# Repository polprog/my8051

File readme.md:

my8051
======

This project contains my experimental FPGA code aiming to program an
8051 software core with several peripherals on the Colorlight 5A-75B
board using the Lattice ECP5 FPGA.

The `r8051.v` and `instruction.v` is the Verilog source code for an
8051 core, by Li Xinbing released under the Apache 2.0 Licence

The main Verilog module is `top.v`. `test.v` is the Icarus Verilog testbench.

The `8051_leds/` directory contains a KiCad project for a small addon
board that plugs on the HUB75 header. It's angled so that its parallel
with the main PCB.

`tools/bin2memh.py` is a script that can convert a file to a hex file
that is loaded with $readmemh directive. This is not an Intel HEX
format.

Currently the project stalled as the core seems to take every jump ;)

Requisites
==========

The code has been tested with Yosys suite for compilation for ECP5.
The makefile uses Icarus Verilog for simulation

You need SDCC assembler for 8051 (sdas8051) to assemble the test
listings. You can also assemble them by hand.

Copying
=======
Unless otherwise stated, the files are

Copyright 2022 polprog

Licensed under the Apache License, Version 2.0 (the "License");
you may not use this file except in compliance with the License.
You may obtain a copy of the License at

    http://www.apache.org/licenses/LICENSE-2.0

Unless required by applicable law or agreed to in writing, software
distributed under the License is distributed on an "AS IS" BASIS,
WITHOUT WARRANTIES OR CONDITIONS OF ANY KIND, either express or implied.
See the License for the specific language governing permissions and
limitations under the License.

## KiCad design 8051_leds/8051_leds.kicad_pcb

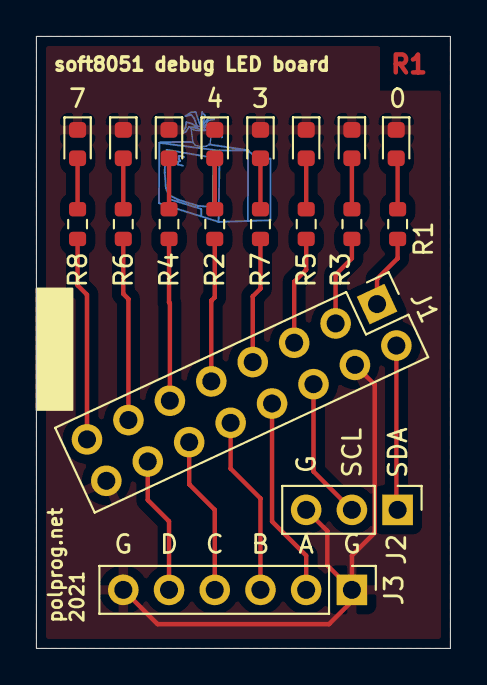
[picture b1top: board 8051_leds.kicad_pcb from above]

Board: 2 copper layers, 23.0 x 34.0 mm, 20 parts (1 on the bottom side), 23 nets.

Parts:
D1, D2, D3, D4, D5, D6, D7, D8: LED_Small; LED_0603_1608Metric
J1: Conn_02x08_Odd_Even; PinHeader_2x08_P2.54mm_Vertical
J2: Conn_01x03; PinHeader_1x03_P2.54mm_Vertical
J3: Conn_01x06; PinHeader_1x06_P2.54mm_Vertical
R1, R2, R3, R4, R5, R6, R7, R8: 1k; R_0603_1608Metric
svg2mod: G***; crt37_small

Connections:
/IOA: J1.8, J3.2
/IOB: J1.10, J3.3
/IOC: J1.12, J3.4
/IOD: J1.14, J3.5
/LED1: J1.1, R1.1
/LED2: J1.3, R3.1
/LED3: J1.5, R5.1
/LED4: J1.7, R7.1
/LED5: J1.9, R2.1
/LED6: J1.11, R4.1
/LED7: J1.13, R6.1
/LED8: J1.15, R8.1
/SCL: J1.6, J2.2
/SDA: J1.2, J2.1
GND: D1.1, D2.1, D3.1, D4.1, D5.1, D6.1, D7.1, D8.1, J1.4, J1.16, J2.3, J3.1, J3.6
unnamed: D1.2, R1.2
unnamed: D2.2, R2.2
unnamed: D3.2, R3.2
unnamed: D4.2, R4.2
unnamed: D5.2, R5.2
unnamed: D6.2, R6.2
unnamed: D7.2, R7.2
unnamed: D8.2, R8.2

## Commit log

2022-09-27 Update readme (2)
